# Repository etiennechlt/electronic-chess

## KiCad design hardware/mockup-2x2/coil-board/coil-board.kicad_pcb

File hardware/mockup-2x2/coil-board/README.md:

# Carte bobines du pilote 2 x 2

Carte 100 x 100 mm, 4 couches, entièrement générée par
`python -m coilgen build` depuis `config/board.yaml` (section
`mockup.coil_board`). Ne pas éditer le `.kicad_pcb` à la main : modifier
le yaml ou le générateur, puis regénérer.

Depuis le 07/10/2026 c'est la carte du **pilote simple** : une seule
carte à concevoir, passive, dans le palier tarifaire 100 x 100 mm, dont
le frontal analogique vit sur un shield à côté de la Nucleo-G474RE. Ce
que le pilote réunit et ce qu'il coûte est dans la
[fiche du pilote](../../../docs/bom-pilote.md).

## Contenu

- 4 spirales de détection (S1 à S4 au pas de 50 mm) : 5 tours par
  couche, 4 couches en série, piste 1,60 mm, espace 0,15 mm, environ
  16 µH par bobine, bornes empilées verticalement et routées en paire
  vers le connecteur.
- Connecteur J1, barrette 1 x 12 au pas 2,54 (ordre des broches : GND,
  C1A, C1B, C3A, C3B, C4A, C4B, C2A, C2B, GND, DIN, 5V), le brochage
  qu'attend la carte analogique (`analoggen`). Les broches 11 et 12
  (DIN, 5V) ne portent aucun cuivre sur la carte passive.
- 4 trous de fixation M3 aux coins (entretoises de 25 mm pour arriver
  au niveau du shield Nucleo).
- 4 trous M3 espacés de 34 mm autour de S3 pour le support d'aimant
  réglable imprimé (répertoire `mechanical/`).
- **Aucun composant** : `mockup.coil_board.leds.fitted` vaut `false`
  dans le yaml. Le mettre à `true` remet les huit WS2812B de camp et
  leurs huit 100 nF de l'ADR 0009, avec leur chaîne de données, leur
  5 V et leur masse ; cette variante éclairée n'a pas été reprise au DRC
  (elle portait 251 violations et deux liaisons ouvertes, voir la
  [note 22](../../../docs/notes/22-erreurs-de-conception.md), points 10
  et 12) et ne se commande pas en l'état.

## Nomenclatures et placement

`python -m coilgen build` écrit, à côté de la carte, `bom.csv`,
`jlc-bom.csv` et `jlc-cpl.csv`. Sur la carte passive ils n'ont que
leur ligne d'en-tête : rien à assembler, rien à placer. La seule pièce
à acheter à part est la barrette mâle 1 x 12 au pas 2,54 (droite, ou
coudée si le shield est coplanaire), à souder à la main, 0,1 USD.

## Ouvrir

`coil-board.kicad_pro`, généré avec la carte, est le fichier à ouvrir
dans KiCad ; il porte la classe de nets et les minima du DRC issus du
yaml : garde 0,13 mm, piste d'interconnexion 0,5 mm, vias 0,6/0,3 mm
pour les bobines, cuivre à 0,5 mm du bord. La carte n'a pas de
schéma : elle est purement passive et toute sa connectivité tient dans
le `.kicad_pcb`.

## Fabrication : commandable (07/10/2026)

```bash
sh hardware/mockup-2x2/coil-board/export.sh
```

Le script regénère la carte puis appelle `tools/gerbers.py`, comme les
autres cartes du dépôt : les plans sont remplis avant le tracé, la pile
de couches est lue sur la carte, et l'export est refusé tant que le
routage n'est pas fermé.

État mesuré par `tools/drc.py` (KiCad 7.0.11) sur le fichier commité :

| Contrôle | Résultat |
|---|---|
| Erreurs de DRC | **0** (gardes, perçages, masque, bord) |
| Éléments non connectés | **0** (7 587 pistes, 12 vias) |
| Avertissements, ignorés par le garde | 9 `lib_footprint_issues` (empreintes embarquées, pas de bibliothèque), 1 copeau de cuivre sur B.Cu sans position, sans effet en fabrication |

Ce qui a fermé la carte, par rapport à son état du 19/09/2026
(251 violations, deux liaisons ouvertes) :

- les LED et leur routage sont coupés par le yaml : tous les perçages
  superposés, toutes les gardes de perçage et presque tous les ponts de
  masque venaient de la chaîne de LED ;
- la bande de masse qui relie les deux broches GND du connecteur passait
  sur les pastilles des broches 2 à 9 (seize défauts) : elle court
  maintenant à 0,6 mm du bord, en 0,5 mm, à 0,55 mm du cuivre des
  pastilles, et le build vérifie cette cote ;
- le repère `J1` s'imprimait sur le bord de la carte : il est à l'ouest
  de la rangée ; les lignes de cases de la sérigraphie s'arrêtent à
  1 mm du bord, là où le fabricant les rognait.

`coil-board-gerbers.zip` se dépose tel quel chez le fabricant, avec son
empreinte à côté :

```bash
cd hardware/mockup-2x2/coil-board && sha256sum -c coil-board-gerbers.sha256
```

Paramètres de commande, formulaire de la
[note 23](../../../docs/notes/23-commande-jlcpcb.md) : 4 couches,
100 x 100 mm, 1,6 mm (l'épaisseur entre dans l'entrefer du modèle),
cuivre externe 1 oz, **cuivre interne 1 oz en option payante** (la
spirale du modèle, note 23 paragraphe 3.1 ; sinon corriger le yaml
avant de mesurer), finition HASL sans plomb (aucun boîtier fin), 5
pièces, pas d'assemblage, numéro de commande retiré ou à emplacement
imposé (la carte est un capteur). Ordre de prix : 8 à 15 EUR les cinq,
10 à 25 EUR de plus pour le cuivre interne, port en sus.

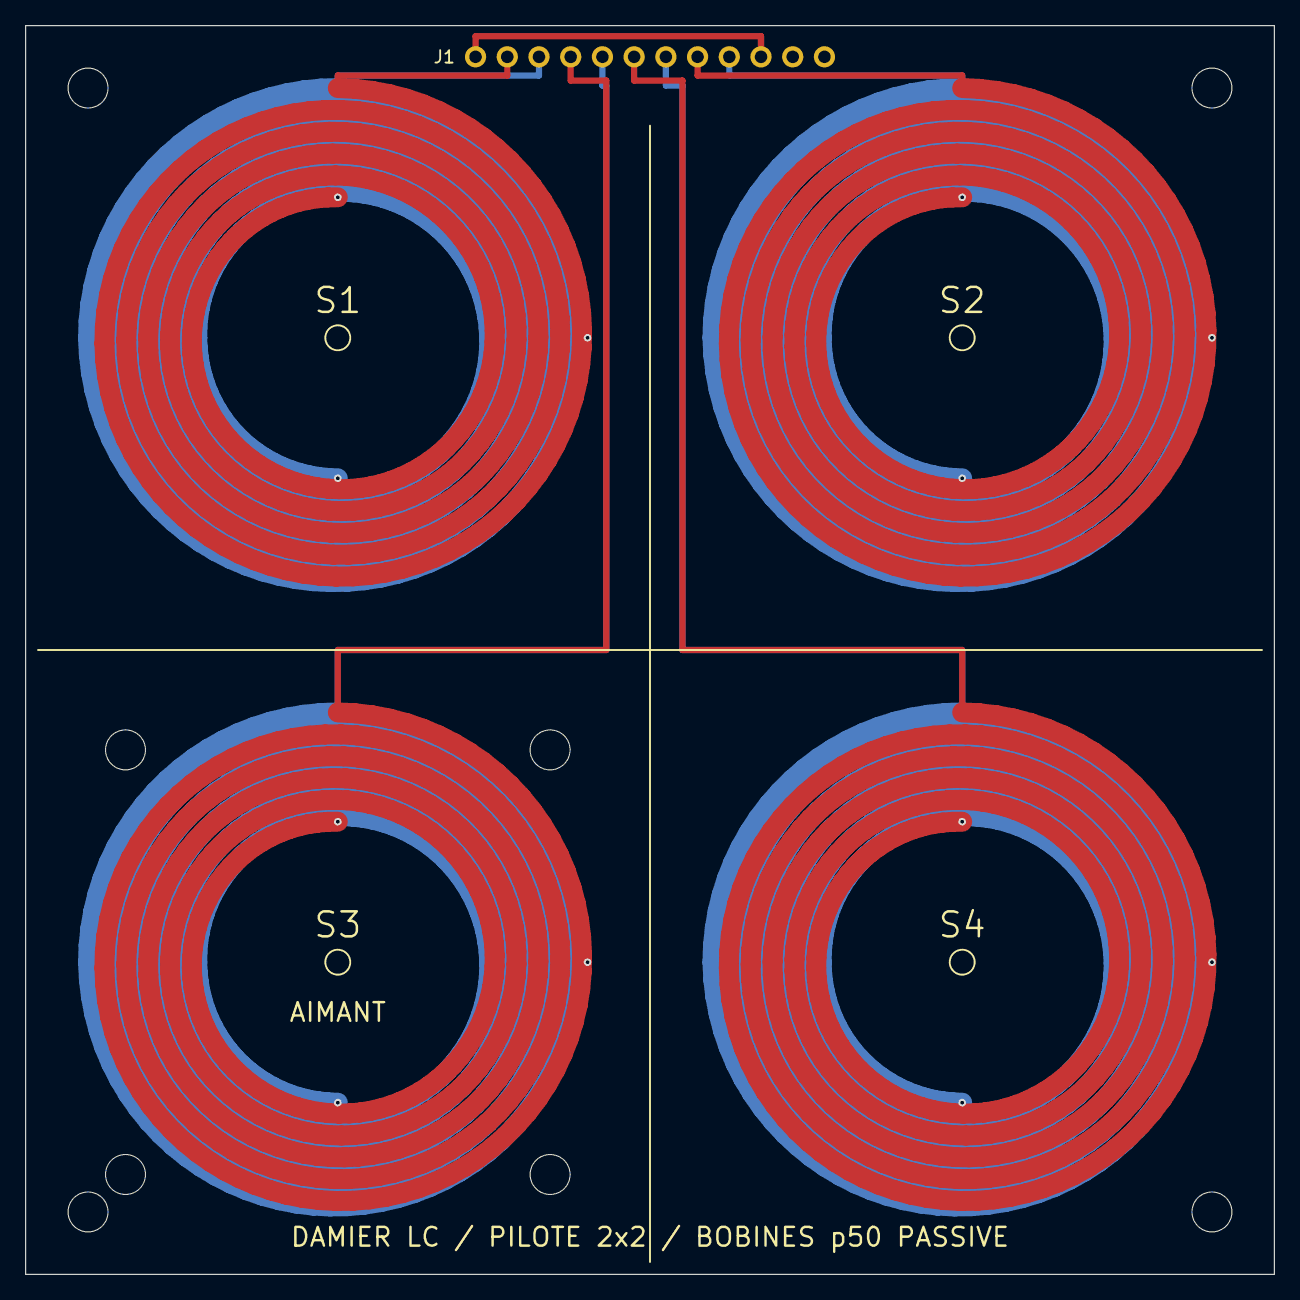
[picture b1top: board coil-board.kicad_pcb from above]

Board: 4 copper layers, 100.0 x 100.0 mm, 9 parts (0 on the bottom side), 5 nets.

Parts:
H1, H2, H3, H4: NPTH; NPTH_3.2
J1: COIL_JOINT_1x12
M1, M2, M3, M4: NPTH; NPTH_3.2

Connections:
C1: J1.2, J1.3
C2: J1.8, J1.9
C3: J1.4, J1.5
C4: J1.6, J1.7
GND: J1.1, J1.10

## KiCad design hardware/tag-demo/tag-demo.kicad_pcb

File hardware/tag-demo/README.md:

# Planche d'étiquettes NFC du démonstrateur Hall + RFID

Carte générée par `python -m taggen build` depuis `config/board.yaml`
(`hall_rfid.mockup.tags`, `hall_rfid.demo.tags`, `hall_rfid.mockup.pickup`)
et le modèle d'étiquette de `chessboard_calc.nfc` (`tag_geometry`,
`tag_tuning`). Ne pas éditer le `.kicad_pcb` à la main : modifier le
yaml ou le générateur, puis regénérer. La fonction, le montage et les
mesures sont dans la [note 27](../../docs/notes/27-demonstrateur-hall-rfid.md).

## Ce que porte la planche

- **100 x 86,5 mm, 2 couches, FR-4 0,8 mm**, rails de 5 mm sur les
  deux grands côtés et barres de 3 mm en haut et en bas, trois mires
  sur les rails.
- **15 étiquettes rondes**, trois de chaque variante, tenues par des
  attaches de 2,5 mm à trous de souris (0,5 mm au pas de 0,75) : la
  rupture se fait au bord du disque, sans ergot.

  | Variante | Disque | Bobine | Accord (modèle) | Pour quelle base |
  |---|---|---|---|---|
  | P | 14,5 mm | 5 + 5 spires, piste et écart 0,20 mm | 17,3 MHz | pion, cavalier, fou (bases de 17,5 à 20 mm à p = 50) |
  | P + 15 pF | 14,5 mm | idem | 15,2 MHz | compromis de la note 25 |
  | P + 22 pF | 14,5 mm | idem | 14,5 MHz | la meilleure marge d'activation, jamais à pleine conductance |
  | G | 19,5 mm | 4 + 4 spires | 16,1 MHz | tour, dame, roi (bases de 22,5 mm) |
  | G + 10 pF | 19,5 mm | idem | 14,7 MHz | la seule G qui tient au pas de 40 |

  Chaque disque : la spirale de la face avant part du centre vers le
  bord, un via au bord, la spirale de la face arrière revient vers le
  centre ; les deux extrémités arrivent sur les broches LA (1) et LB
  (8) de la puce **NT3H2111W0FTTJ** (NXP NTAG I2C plus, TSSOP8,
  soudable au fer), posée au centre ; un condensateur 0402 C0G d'accord
  entre LA et LB, monté sur les variantes qui en portent un. Les broches
  I2C, FD, VCC, VSS et VOUT restent en l'air : la puce vit du champ du
  lecteur. Le disque entre dans l'alésage de la base d'une pièce, puce
  vers le haut, tenu par un ruban polyimide (note 25, paragraphe 5).
- **La vignette de champ** (17 x 14,5 mm, en bas à droite) : une bobine
  de 10 mm à 2 + 2 spires, une diode Schottky à faible seuil
  (BAT15-03W, SOD-323), 1 nF et 100 kΩ en charge, deux pastilles pour
  les fils torsadés vers l'entrée `PICKUP` de la carte principale. Les
  trois composants se soudent à la main. Étalonnée contre le NanoVNA,
  elle donne une mesure relative du champ sans oscilloscope.

## Nomenclatures

`bom.csv` liste les 15 puces, les 9 condensateurs d'accord montés (3 x
10 pF, 3 x 15 pF, 3 x 22 pF), les 6 emplacements non montés et les trois
composants de la vignette. `jlc-bom.csv` et `jlc-cpl.csv` ne portent que
les lignes à code LCSC : le code de la puce en TSSOP8 et ceux des 0402
C0G sont à relever au panier (la puce en XQFN8, C710403, est l'autre
option si JLCPCB doit poser les puces : même brochage, empreinte à
changer dans le générateur). Sans assemblage, la planche se commande
nue et les puces se soudent au fer : 0,65 mm de pas, flux, une broche
d'ancrage puis les autres.

## Régénérer et vérifier

```bash
PYTHONPATH=tools .venv/bin/python -m taggen build --render docs/images/tag-demo.png
/usr/bin/python3 tools/drc.py hardware/tag-demo/tag-demo.kicad_pcb
/usr/bin/python3 tools/gerbers.py hardware/tag-demo/tag-demo.kicad_pcb
cd hardware/tag-demo && sha256sum -c tag-demo-gerbers.sha256
```

DRC KiCad 7.0.11 sur le fichier commité : zéro erreur, zéro élément
non connecté (les avertissements restants sont les chemins de
bibliothèque des empreintes et quelques repères de sérigraphie sur la
vignette). `tag-demo-gerbers.zip` se dépose tel quel chez JLCPCB :
2 couches, 0,8 mm, HASL, « Panel by Customer », quatre conceptions
déclarées (P, G, vignette et le cadre), 5 pièces. Options écran par
écran dans la note 27.

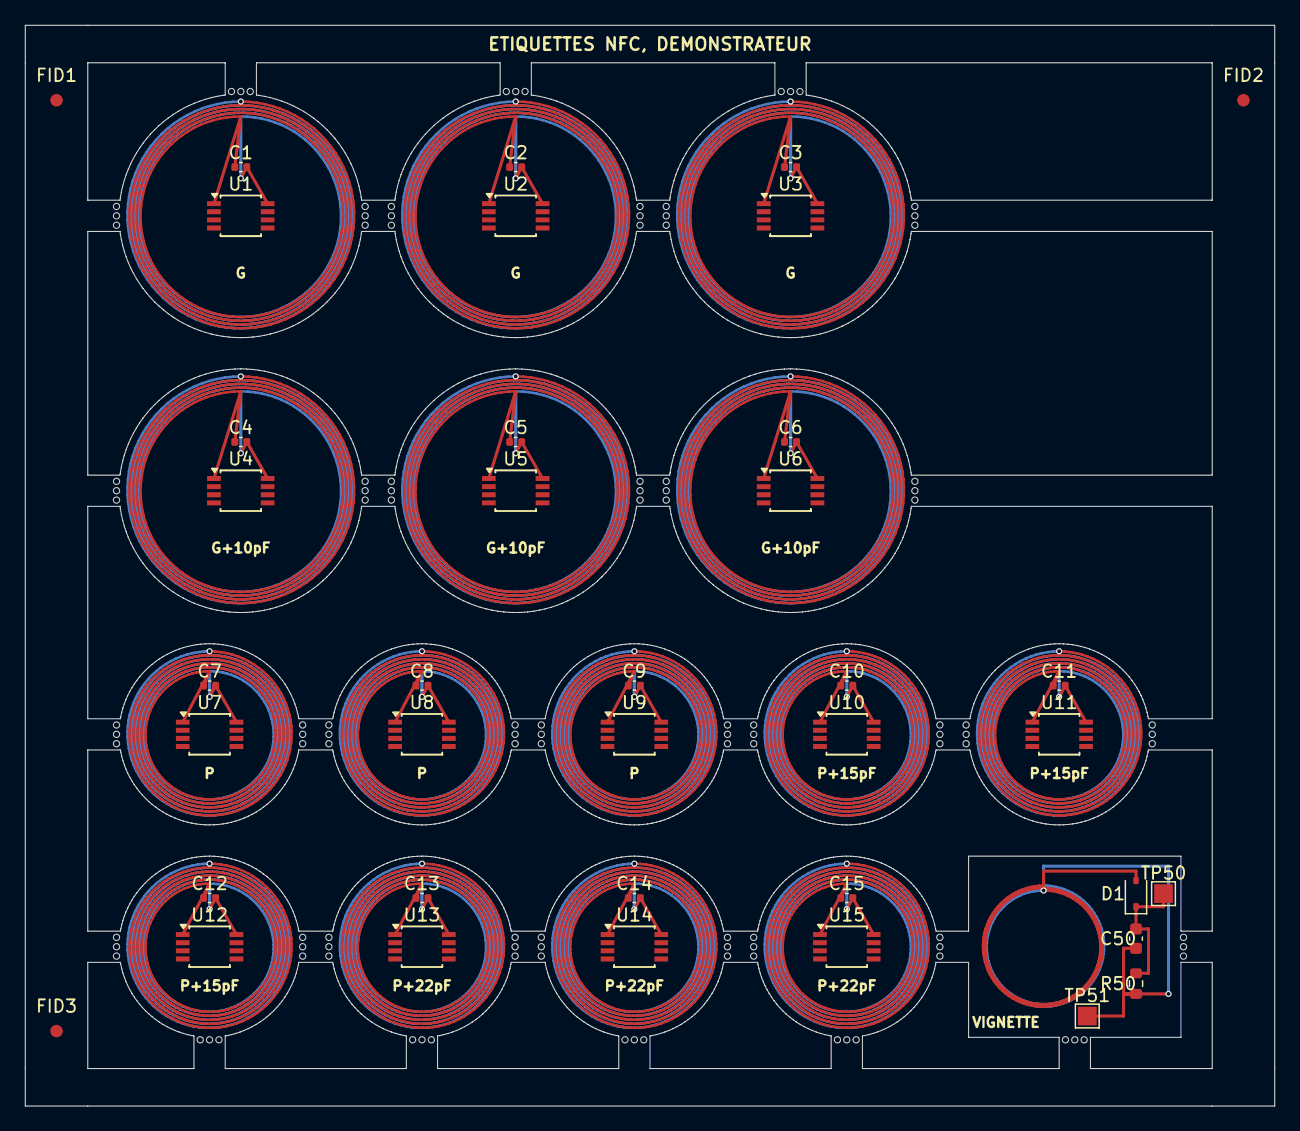
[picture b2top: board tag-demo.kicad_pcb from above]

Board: 2 copper layers, 100.0 x 86.5 mm, 155 parts (0 on the bottom side), 17 nets.

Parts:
C1, C2, C3, C7, C8, C9: non montee; C_0402_1005Metric
C4, C5, C6: 10p; C_0402_1005Metric
C10, C11, C12: 15p; C_0402_1005Metric
C13, C14, C15: 22p; C_0402_1005Metric
C50: 1n; C_0603_1608Metric
D1: BAT15-03W; D_SOD-323
FID1, FID2, FID3: Fiducial; Fiducial_1mm_Mask2mm
MB1, MB2, MB3, MB4, MB5, MB6, MB7, MB8, MB9, MB10, MB11, MB12, MB13, MB14, MB15, MB16, MB17, MB18, MB19, MB20, MB21, MB22, MB23, MB24, MB25, MB26, MB27, MB28, MB29, MB30, MB31, MB32, MB33, MB34, MB35, MB36, MB37, MB38, MB39, MB40, MB41, MB42, MB43, MB44, MB45, MB46, MB47, MB48, MB49, MB50, MB51, MB52, MB53, MB54, MB55, MB56, MB57, MB58, MB59, MB60, MB61, MB62, MB63, MB64, MB65, MB66, MB67, MB68, MB69, MB70, MB71, MB72, MB73, MB74, MB75, MB76, MB77, MB78, MB79, MB80, MB81, MB82, MB83, MB84, MB85, MB86, MB87, MB88, MB89, MB90, MB91, MB92, MB93, MB94, MB95, MB96, MB97, MB98, MB99, MB100, MB101, MB102, MB103, MB104, MB105, MB106, MB107, MB108, MB109, MB110, MB111, MB112, MB113, MB114, MB115, MB116, MB117: NPTH; NPTH_0.5
R50: 100k; R_0603_1608Metric
TP50: PK_OUT; TestPoint_Pad_1.5x1.5mm
TP51: PK_COIL; TestPoint_Pad_1.5x1.5mm
U1, U2, U3: NT3H2111 G; TSSOP-8_3x3mm_P0.65mm
U4, U5, U6: NT3H2111 G+10pF; TSSOP-8_3x3mm_P0.65mm
U7, U8, U9: NT3H2111 P; TSSOP-8_3x3mm_P0.65mm
U10, U11, U12: NT3H2111 P+15pF; TSSOP-8_3x3mm_P0.65mm
U13, U14, U15: NT3H2111 P+22pF; TSSOP-8_3x3mm_P0.65mm

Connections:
PK_COIL: C50.1, D1.2, R50.1, TP51.1
PK_OUT: C50.2, D1.1, R50.2, TP50.1
T1: C1.1, C1.2, U1.1, U1.8
T2: C2.1, C2.2, U2.1, U2.8
T3: C3.1, C3.2, U3.1, U3.8
T4: C4.1, C4.2, U4.1, U4.8
T5: C5.1, C5.2, U5.1, U5.8
T6: C6.1, C6.2, U6.1, U6.8
T7: C7.1, C7.2, U7.1, U7.8
T8: C8.1, C8.2, U8.1, U8.8
T9: C9.1, C9.2, U9.1, U9.8
T10: C10.1, C10.2, U10.1, U10.8
T11: C11.1, C11.2, U11.1, U11.8
T12: C12.1, C12.2, U12.1, U12.8
T13: C13.1, C13.2, U13.1, U13.8
T14: C14.1, C14.2, U14.1, U14.8
T15: C15.1, C15.2, U15.1, U15.8

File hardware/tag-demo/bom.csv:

References,Qty,Value,Footprint,MPN,LCSC,DNP
C1 C2 C3 C7 C8 C9,6,non montee,C_0402_1005Metric,,,DNP
C10 C11 C12,3,15p,C_0402_1005Metric,,,
C13 C14 C15,3,22p,C_0402_1005Metric,,,
C4 C5 C6,3,10p,C_0402_1005Metric,,,
C50,1,1n,C_0603_1608Metric,,C1588,
D1,1,BAT15-03W,D_SOD-323,BAT15-03W,,
R50,1,100k,R_0603_1608Metric,,C25803,
U1 U2 U3,3,NT3H2111 G,TSSOP-8_3x3mm_P0.65mm,NT3H2111W0FTTJ,,
U10 U11 U12,3,NT3H2111 P+15pF,TSSOP-8_3x3mm_P0.65mm,NT3H2111W0FTTJ,,
U13 U14 U15,3,NT3H2111 P+22pF,TSSOP-8_3x3mm_P0.65mm,NT3H2111W0FTTJ,,
U4 U5 U6,3,NT3H2111 G+10pF,TSSOP-8_3x3mm_P0.65mm,NT3H2111W0FTTJ,,
U7 U8 U9,3,NT3H2111 P,TSSOP-8_3x3mm_P0.65mm,NT3H2111W0FTTJ,,
